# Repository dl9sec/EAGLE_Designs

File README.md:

# EAGLE Designs
Some designs created with EAGLE 6.6.0.

# Contents

<dl>
  <dt>ESP32VGAv2 (License CC BY-SA 4.0)</dt>
  <dd>An ESP-32 DevKitC base board with 6-bit VGA, DAC sound output and PS/2 keyboard connector. The design can be used with FabGL by fdivitto (https://github.com/fdivitto/FabGL) and with ESP32Lib by bitluni (https://github.com/bitluni/ESP32Lib). The folder contains a ready-to-use ZIP-archive with Gerber/Excellon data which can be directly used at JLCPCB.com.</dd>
  <dt>ESP32-XTonUINO/ESP32-XTonUINO_Buttons (License GPL-3.0-only)</dt>
  <dd>An ESP-32 DevKitC base board which can be used for a TonUINO player (e.g. with adapted sources of CKUL's TonUINO-ESP project at https://github.com/CKUL/TonUINO-ESP32 or one of its forks). The base design is extended by capacitive touch buttons and a relay which can be used e.g. for a door opener. The design uses a module for charging a LiPo/LiIon recharchable battery and a boost converter module to supply the board from the battery. The folder contains ready-to-use ZIP-archives with Gerber/Excellon data which can be directly used at JLCPCB.com.</dd>
  <dt>JLCPCB_CAMjob (License MIT)</dt>
  <dd>A CAM job to generate the Gerber/EXCELLON data for JLCPCB.com in one pass (ZIP the generated files before upload!).</dd>

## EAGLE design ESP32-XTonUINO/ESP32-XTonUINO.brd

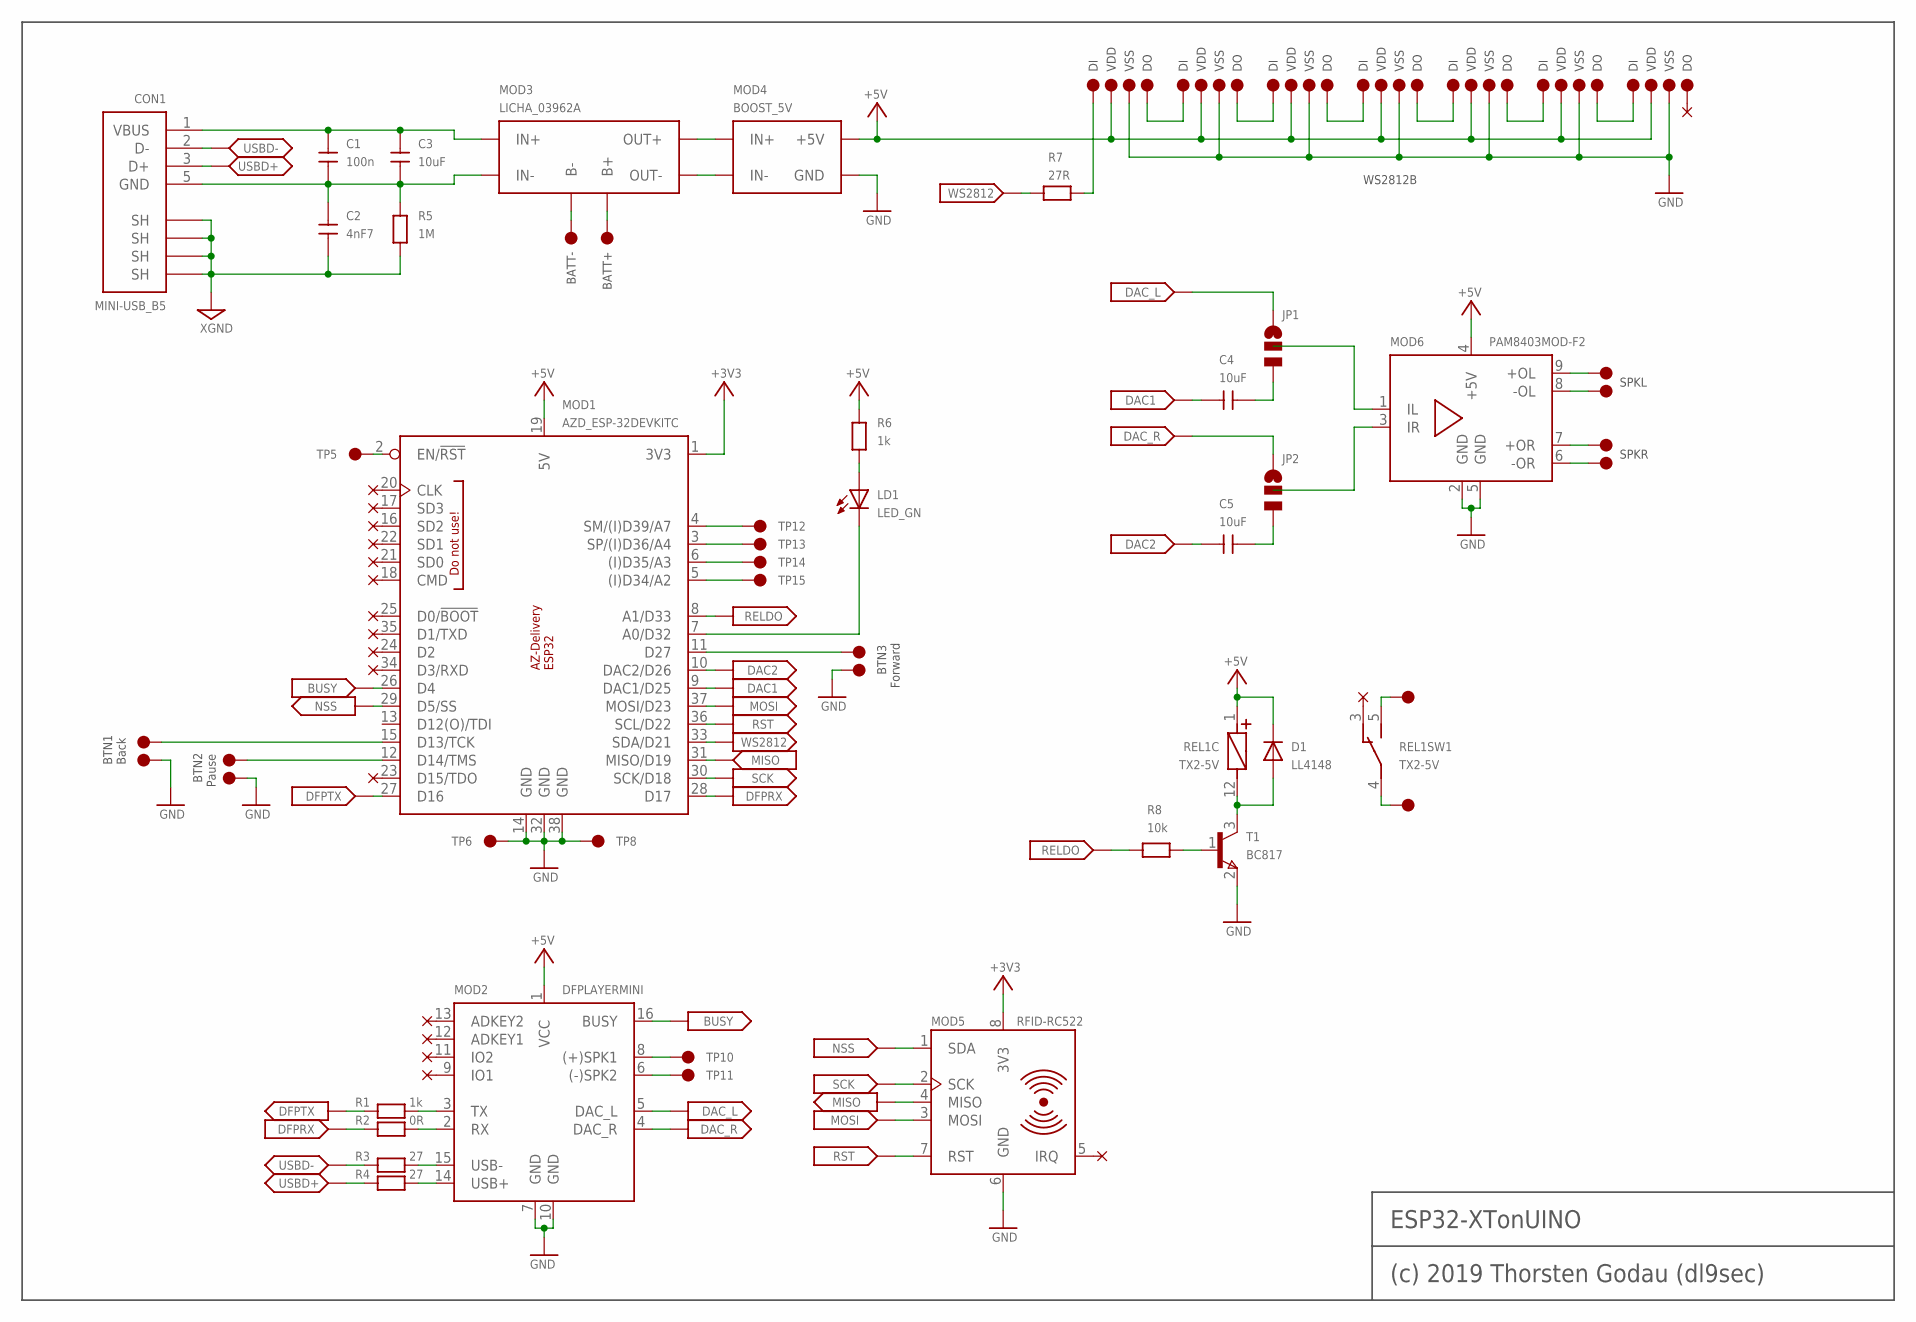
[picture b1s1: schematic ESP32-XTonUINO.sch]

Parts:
C1: 100n; 0805
C2: 4nF7; 0805
C3, C4, C5: 10uF; 0805
CON1: MINI-USB_B5; MINIUSB_B5
D1: LL4148; MINIMELF
JP1, JP2: JUMPER_1X3SMD; JUMPER_1X3_SMD
LD1: LED_GN; LED3MMH
MOD1: AZD_ESP-32DEVKITC
MOD2: DFPLAYERMINI
MOD3: LICHA_03962A
MOD4: BOOST_5V
MOD5: RFID-RC522
MOD6: PAM8403MOD-F2; PAM8403MOD2
R1, R6: 1k; 0805
R2: 0R; 0805
R3, R4: 27; 0805
R5: 1M; 0805
R7: 27R; 0805
R8: 10k; 0805
REL1: TX2-5V; RELTX2
T1: BC817; SOT23
TP1, TP2, TP3, TP4, TP5, TP6, TP7, TP8, TP9, TP12, TP13, TP14, TP15, TP16, TP17, TP18, TP19, TP20, TP21, TP22, TP23, TP24, TP25, TP26, TP27, TP28, TP29, TP30, TP31, TP32, TP33, TP34, TP35, TP36, TP37, TP38, TP39, TP40, TP45, TP48, TP49, TP50, TP51: TESTPINTHT1; TESTPIN_THT1
TP10, TP11, TP41, TP42, TP43, TP44, TP46, TP47: TESTPINTHT2; TESTPIN_THT2

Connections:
+3V3: MOD1.1 (3V3), MOD5.8 (3V3)
+5V: D1.K, MOD1.19 (5V), MOD2.1 (VCC), MOD4.+5V, MOD6.4 (+5V), R6.2, REL1.1 (+), TP19.1, TP23.1, TP27.1, TP31.1, TP35.1, TP39.1, TP49.1
BATT+: MOD3.B+, TP9.1
BATT-: MOD3.B-, TP7.1
BTN1: MOD1.15 (D13/TCK), TP1.1
BTN2: MOD1.12 (D14/TMS), TP3.1
BTN3: MOD1.11 (D27), TP16.1
BUSY: MOD1.26 (D4), MOD2.16 (BUSY)
DAC1: C4.1, MOD1.9 (DAC1/D25)
DAC2: C5.1, MOD1.10 (DAC2/D26)
DAC_L: JP1.1, MOD2.5 (DAC_L)
DAC_R: JP2.1, MOD2.4 (DAC_R)
DFPRX: MOD1.28 (D17), R2.1
DFPTX: MOD1.27 (D16), R1.1
GND: MOD1.14 (GND), MOD1.32 (GND), MOD1.38 (GND), MOD2.7 (GND), MOD2.10 (GND), MOD4.GND, MOD5.6 (GND), MOD6.2 (GND), MOD6.5 (GND), T1.2 (E), TP2.1, TP4.1, TP6.1, TP8.1, TP17.1, TP20.1, TP24.1, TP28.1, TP32.1, TP36.1, TP40.1, TP50.1
MISO: MOD1.31 (MISO/D19), MOD5.4 (MISO)
MOSI: MOD1.37 (MOSI/D23), MOD5.3 (MOSI)
unnamed: C1.1, C2.2, C3.1, CON1.5 (GND), MOD3.IN-, R5.2
unnamed: MOD2.14 (USB+), R4.2
unnamed: MOD1.4 (SM/(I)D39/A7), TP12.1
unnamed: MOD1.3 (SP/(I)D36/A4), TP13.1
unnamed: MOD3.OUT-, MOD4.IN-
unnamed: MOD1.6 ((I)D35/A3), TP14.1
unnamed: MOD1.5 ((I)D34/A2), TP15.1
unnamed: MOD1.2 (EN/!RST!), TP5.1
unnamed: C4.2, JP1.3
unnamed: LD1.A, R6.1
unnamed: JP2.2, MOD6.3 (IR)
unnamed: MOD2.15 (USB-), R3.2
unnamed: JP1.2, MOD6.1 (IL)
unnamed: C5.2, JP2.3
unnamed: TP21.1, TP22.1
unnamed: MOD6.9 (+OL), TP41.1
unnamed: MOD2.2 (RX), R2.2
unnamed: MOD2.3 (TX), R1.2
unnamed: MOD6.8 (-OL), TP42.1
unnamed: MOD6.7 (+OR), TP43.1
unnamed: MOD6.6 (-OR), TP44.1
unnamed: TP25.1, TP26.1
unnamed: TP29.1, TP30.1
unnamed: TP33.1, TP34.1
unnamed: TP37.1, TP38.1
unnamed: TP45.1, TP48.1
unnamed: REL1.4 (COM), TP47.1
unnamed: REL1.5 (NO), TP46.1
unnamed: R7.2, TP18.1
unnamed: D1.A, REL1.12 (-), T1.3 (C)
unnamed: R8.2, T1.1 (B)
NLED: LD1.K, MOD1.7 (A0/D32)
NSS: MOD1.29 (D5/SS), MOD5.1 (SDA)
OUT+: MOD3.OUT+, MOD4.IN+
RELDO: MOD1.8 (A1/D33), R8.1
RST: MOD1.36 (SCL/D22), MOD5.7 (RST)
SCK: MOD1.30 (SCK/D18), MOD5.2 (SCK)
SPK+: MOD2.8 ((+)SPK1), TP10.1
SPK-: MOD2.6 ((-)SPK2), TP11.1
USBD+: CON1.3 (D+), R4.1
USBD-: CON1.2 (D-), R3.1
VBUS: C1.2, C3.2, CON1.1 (VBUS), MOD3.IN+
WS2812: MOD1.33 (SDA/D21), R7.1
XGND: C2.1, CON1.S1 (SH), CON1.S2 (SH), CON1.S3 (SH), CON1.S4 (SH), R5.1

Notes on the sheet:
(c) 2019 Thorsten Godau (dl9sec)
BTN3
BTN2
BTN1
Back
Pause
Forward
VDD
VSS
WS2812B
SPKL
SPKR
BATT-
BATT+
ESP32-XTonUINO

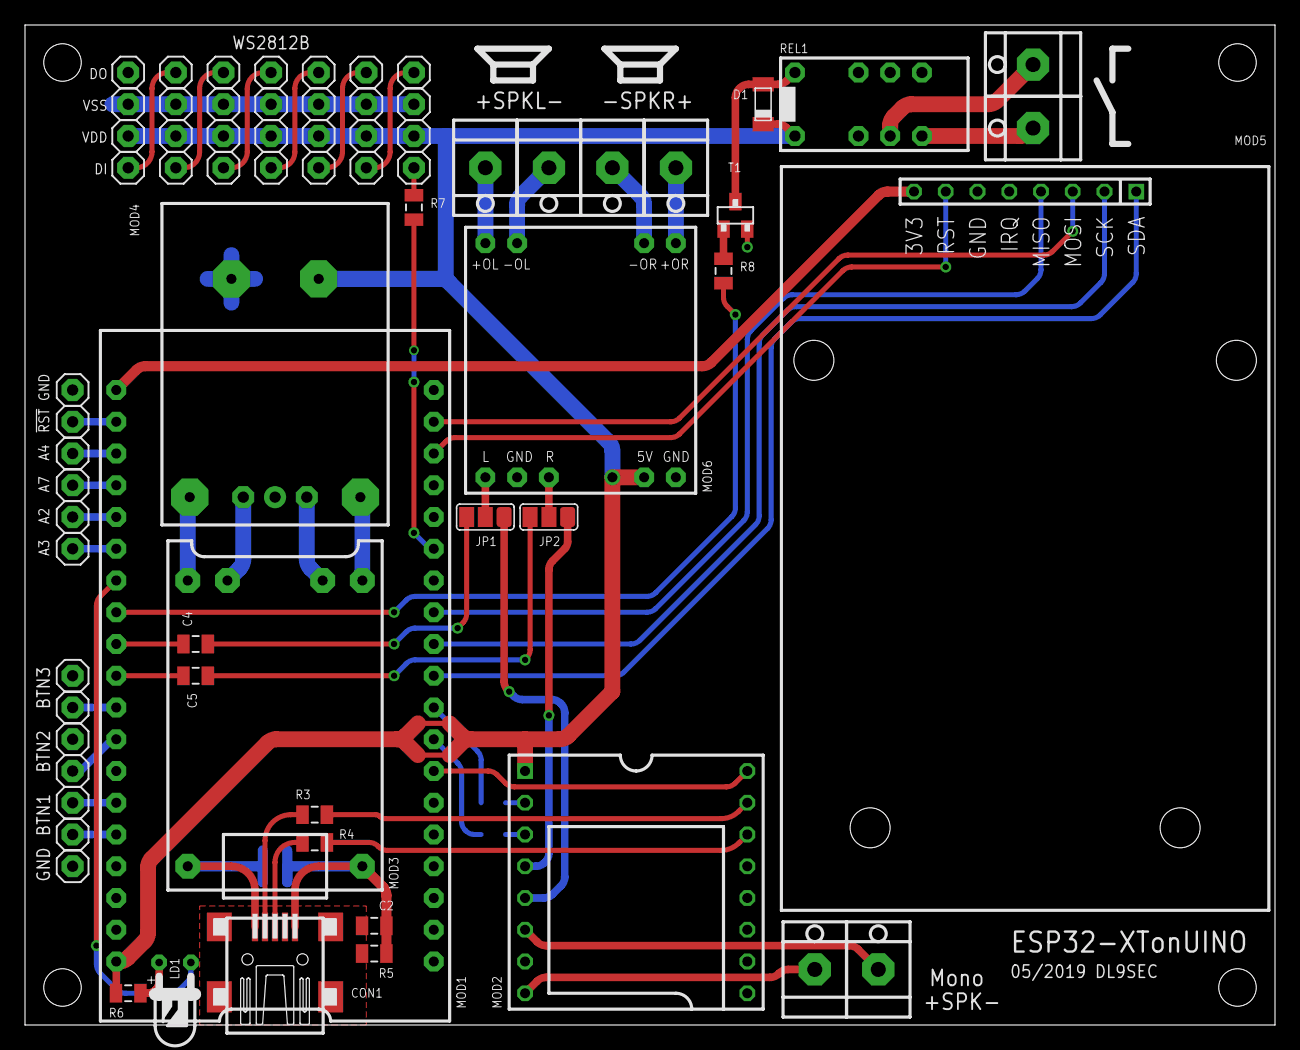
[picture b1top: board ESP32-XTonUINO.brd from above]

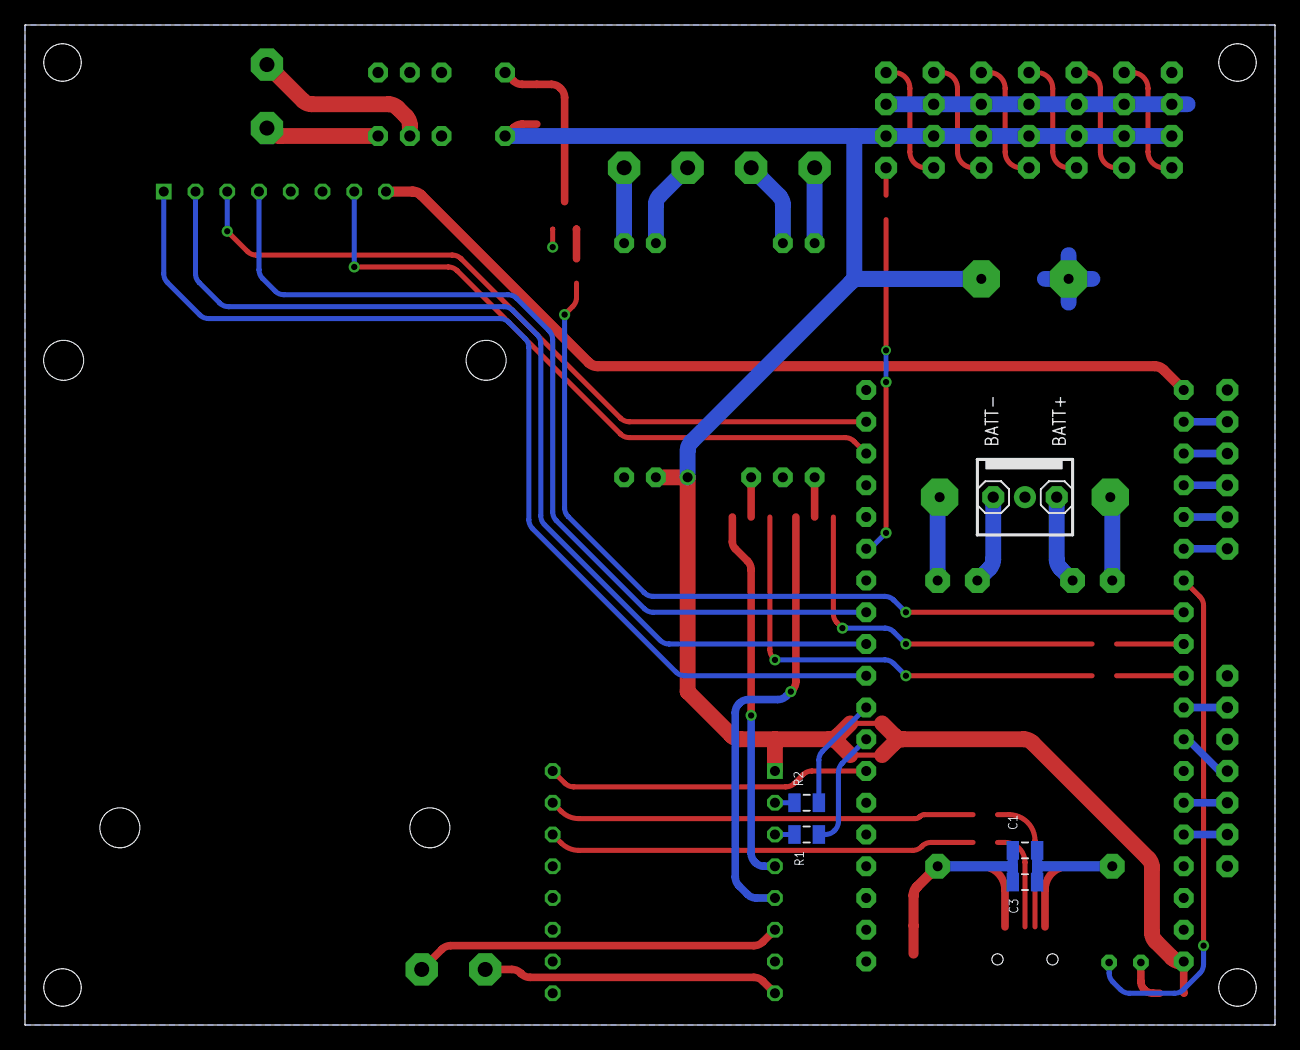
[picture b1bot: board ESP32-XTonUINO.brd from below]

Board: 2 copper layers, 100.0 x 80.0 mm, 77 parts (6 on the bottom side), 61 nets.

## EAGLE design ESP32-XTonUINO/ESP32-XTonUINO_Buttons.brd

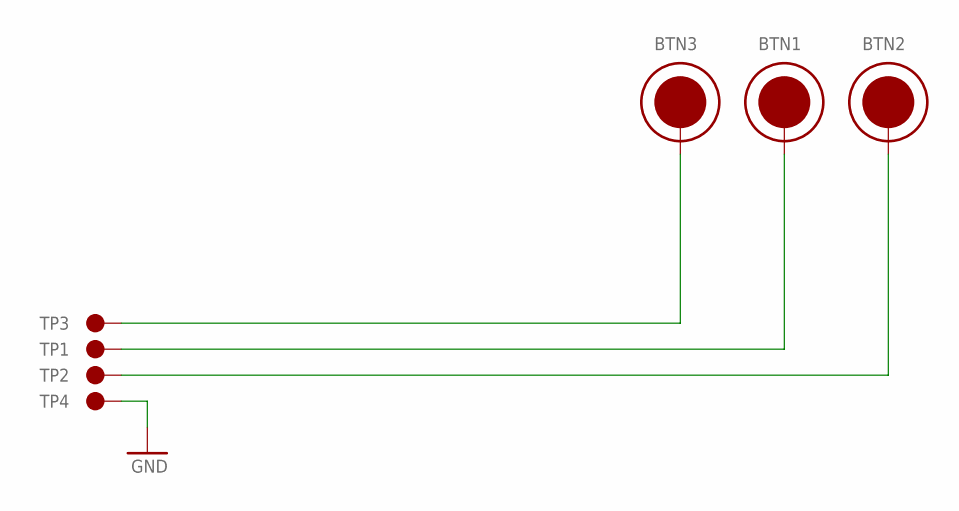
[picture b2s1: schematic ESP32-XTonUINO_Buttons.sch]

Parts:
BTN1, BTN2, BTN3: TOUCHBTN
TP1, TP2, TP3, TP4: TESTPINL; TESTPAD_L

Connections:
GND: TP4.TP
unnamed: BTN3.BTN, TP3.TP
unnamed: BTN1.BTN, TP1.TP
unnamed: BTN2.BTN, TP2.TP

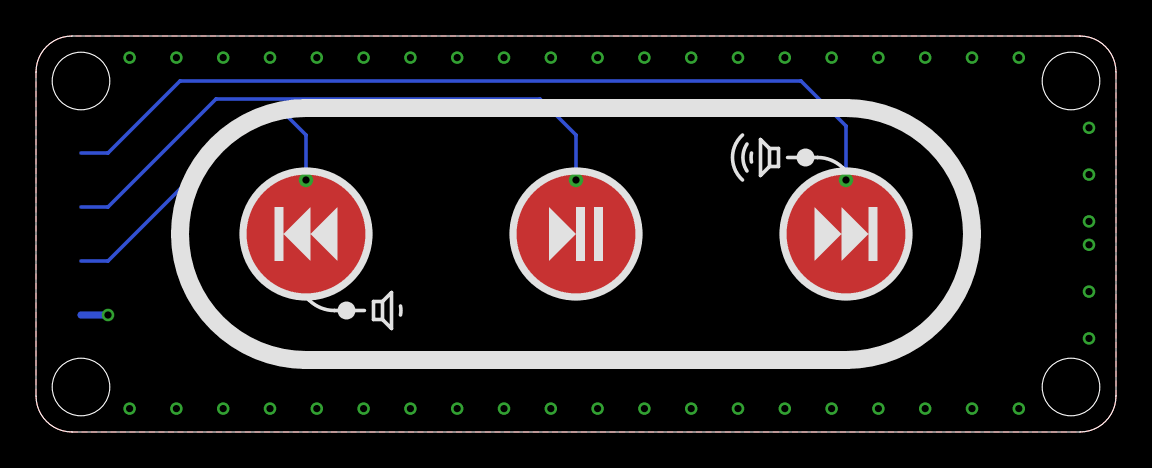
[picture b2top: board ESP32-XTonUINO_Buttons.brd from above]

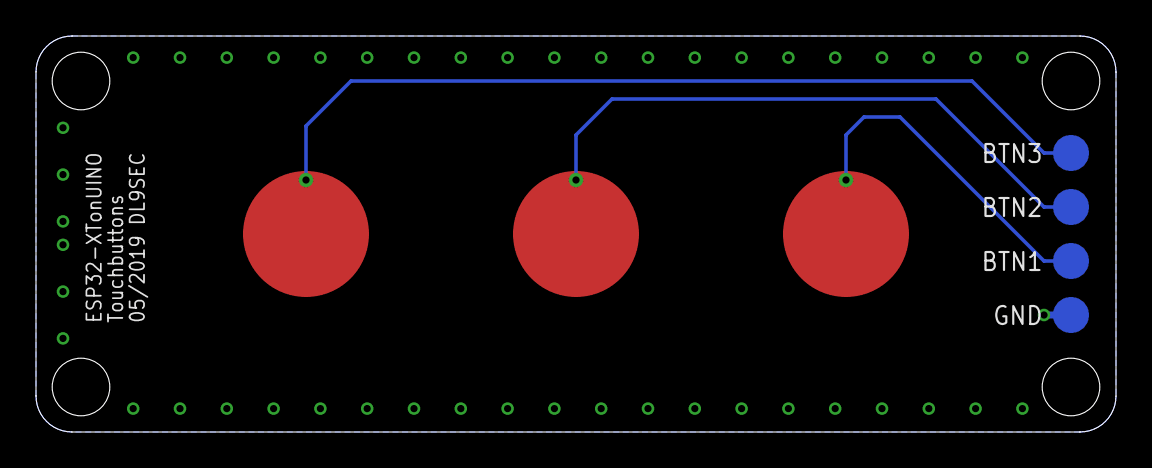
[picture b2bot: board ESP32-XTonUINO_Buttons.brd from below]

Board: 2 copper layers, 60.0 x 22.0 mm, 7 parts (4 on the bottom side), 3 nets.

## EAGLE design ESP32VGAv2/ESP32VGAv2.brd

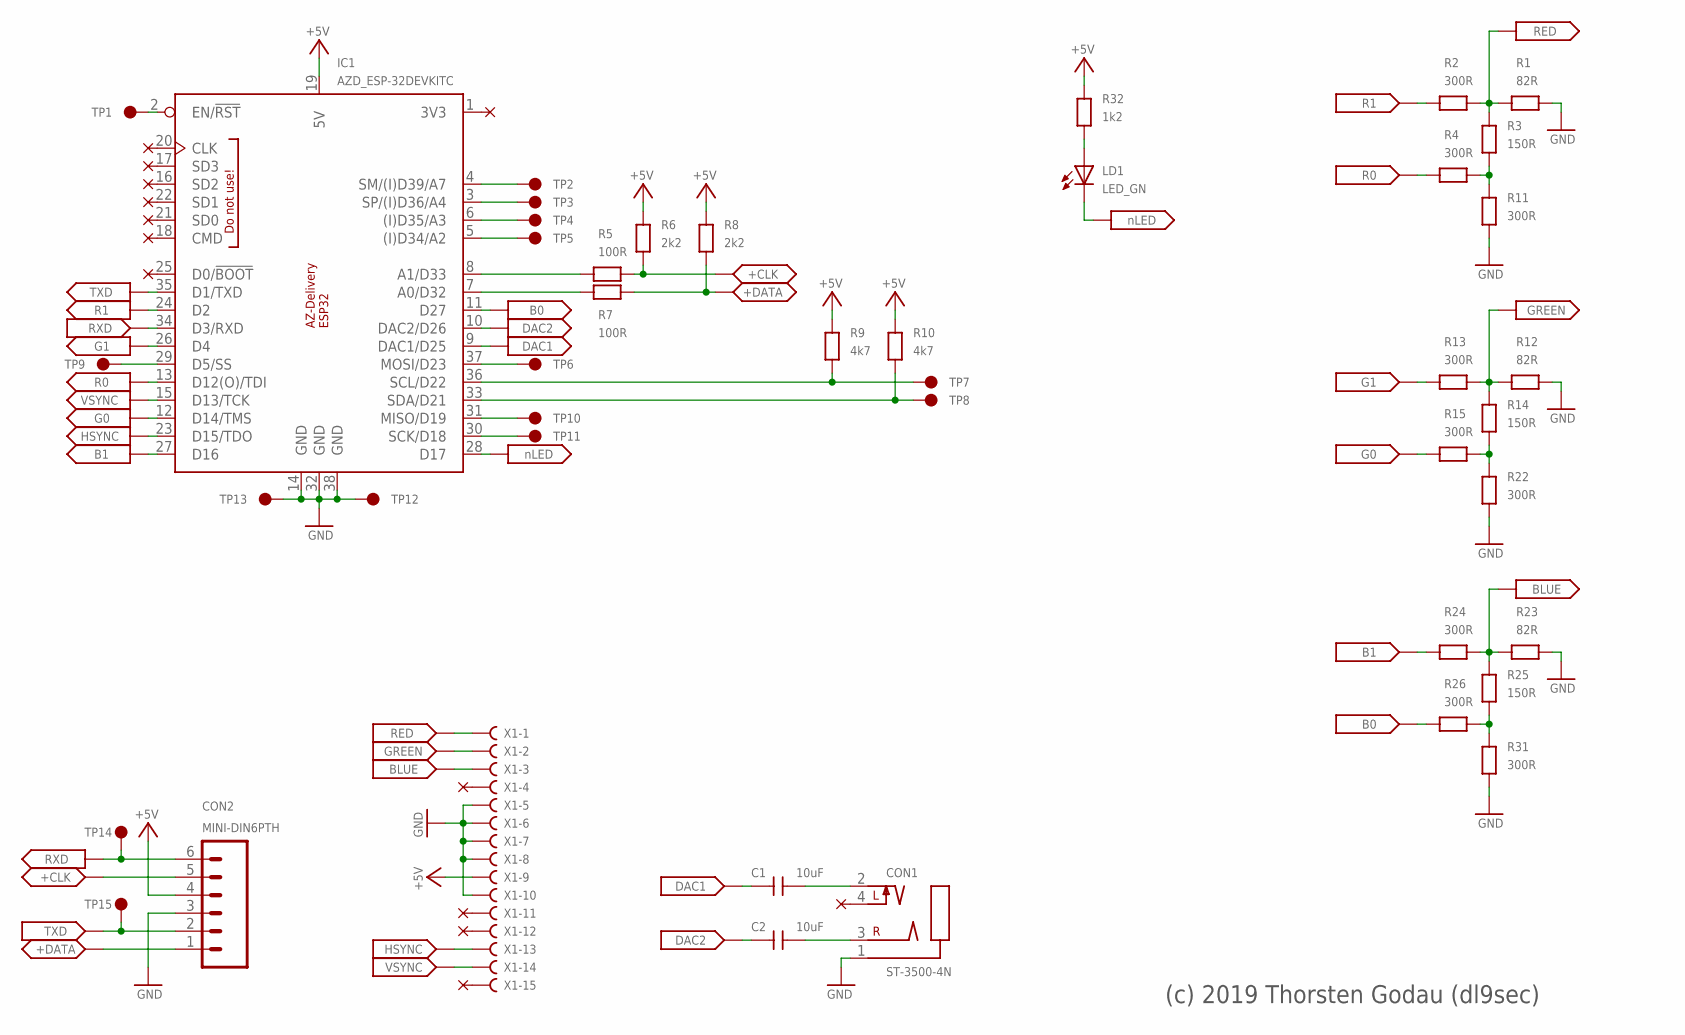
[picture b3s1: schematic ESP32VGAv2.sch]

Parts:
C1, C2: 10uF; 0805
CON1: ST-3500-4N
CON2: MINI-DIN6PTH; MINI-DIN6
IC1: AZD_ESP-32DEVKITC
LD1: LED_GN; LED3MMH
R1, R12, R23: 82R; 0805
R2, R4, R11, R13, R15, R22, R24, R26, R31: 300R; 0805
R3, R14, R25: 150R; 0805
R5, R7: 100R; 0805
R6, R8: 2k2; 0805
R9, R10: 4k7; 0805
R32: 1k2; 0805
TP1, TP2, TP3, TP4, TP5, TP6, TP7, TP8, TP9, TP10, TP11, TP12, TP13, TP14, TP15: TESTPINTHT; TESTPIN_THT
X1: HF15HS; HDF15H

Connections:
+5V: CON2.4, IC1.19 (5V), R6.2, R8.2, R9.2, R10.2, R32.2, X1.9
+CLK: CON2.5, R5.2, R6.1
+DATA: CON2.1, R7.2, R8.1
B0: IC1.11 (D27), R26.1
B1: IC1.27 (D16), R24.1
BLUE: R23.1, R24.2, R25.2, X1.3
DAC1: C1.1, IC1.9 (DAC1/D25)
DAC2: C2.1, IC1.10 (DAC2/D26)
G0: IC1.12 (D14/TMS), R15.1
G1: IC1.26 (D4), R13.1
GND: CON1.1 (COM), CON2.3, IC1.14 (GND), IC1.32 (GND), IC1.38 (GND), R1.2, R11.1, R12.2, R22.1, R23.2, R31.1, TP12.1, TP13.1, X1.5, X1.6, X1.7, X1.8, X1.10
GREEN: R12.1, R13.2, R14.2, X1.2
HSYNC: IC1.23 (D15/TDO), X1.13
KBD_CLK: IC1.8 (A1/D33), R5.1
KBD_DATA: IC1.7 (A0/D32), R7.1
unnamed: R14.1, R15.2, R22.2
unnamed: IC1.4 (SM/(I)D39/A7), TP2.1
unnamed: IC1.3 (SP/(I)D36/A4), TP3.1
unnamed: R3.1, R4.2, R11.2
unnamed: IC1.6 ((I)D35/A3), TP4.1
unnamed: IC1.5 ((I)D34/A2), TP5.1
unnamed: IC1.2 (EN/!RST!), TP1.1
unnamed: C1.2, CON1.2 (L)
unnamed: LD1.A, R32.1
unnamed: IC1.29 (D5/SS), TP9.1
unnamed: R25.1, R26.2, R31.2
unnamed: IC1.30 (SCK/D18), TP11.1
unnamed: IC1.31 (MISO/D19), TP10.1
unnamed: C2.2, CON1.3 (R)
unnamed: IC1.33 (SDA/D21), R10.1, TP8.1
unnamed: IC1.36 (SCL/D22), R9.1, TP7.1
unnamed: IC1.37 (MOSI/D23), TP6.1
NLED: IC1.28 (D17), LD1.K
R0: IC1.13 (D12(O)/TDI), R4.1
R1: IC1.24 (D2), R2.1
RED: R1.1, R2.2, R3.2, X1.1
RXD: CON2.6, IC1.34 (D3/RXD), TP14.1
TXD: CON2.2, IC1.35 (D1/TXD), TP15.1
VSYNC: IC1.15 (D13/TCK), X1.14

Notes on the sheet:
(c) 2019 Thorsten Godau (dl9sec)

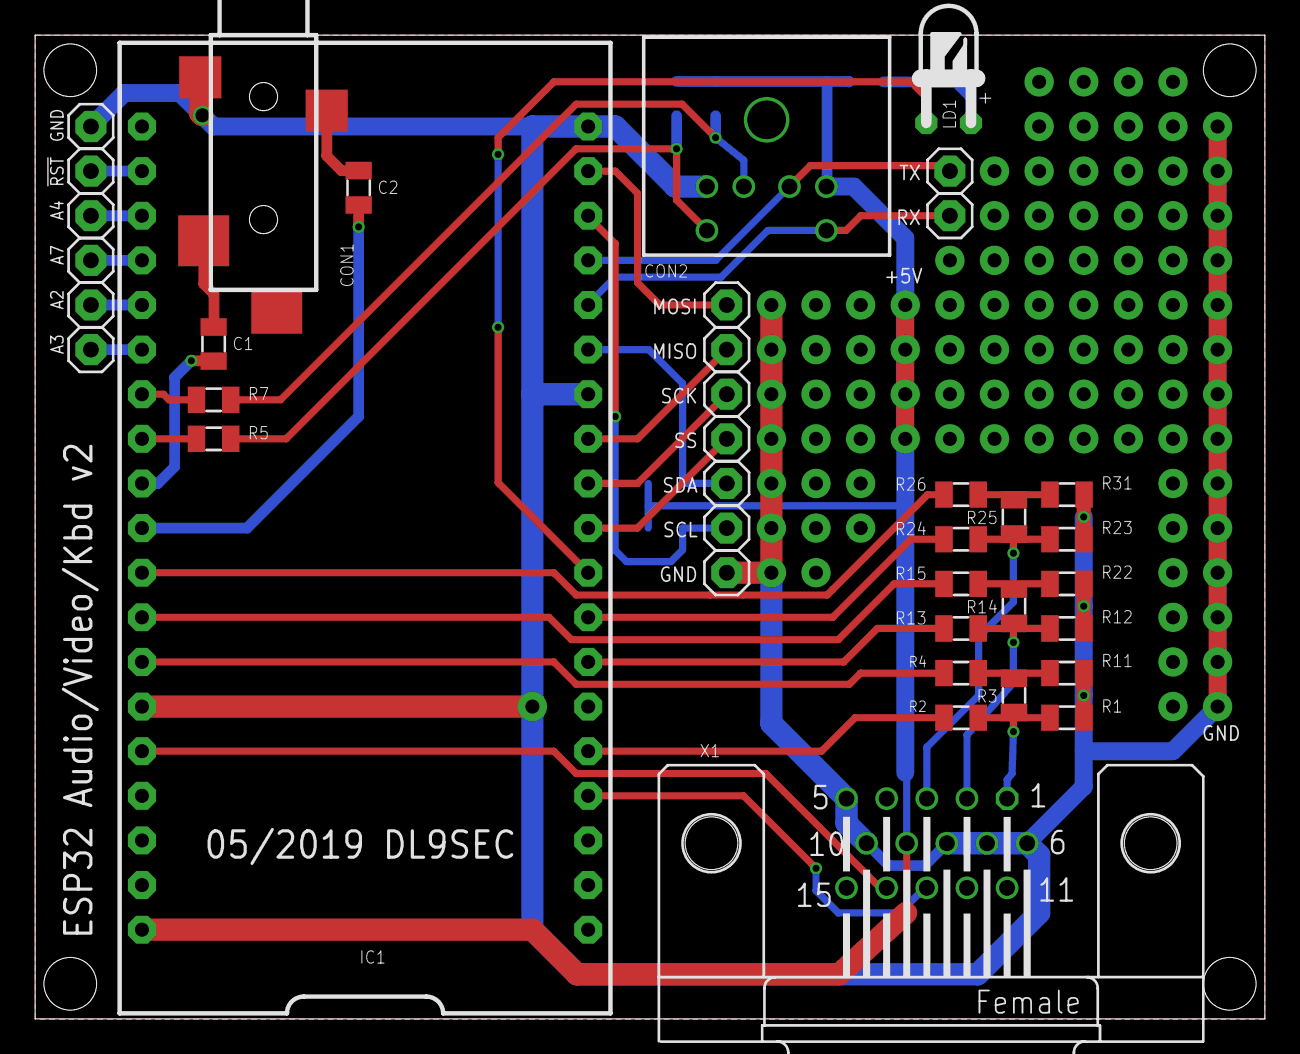
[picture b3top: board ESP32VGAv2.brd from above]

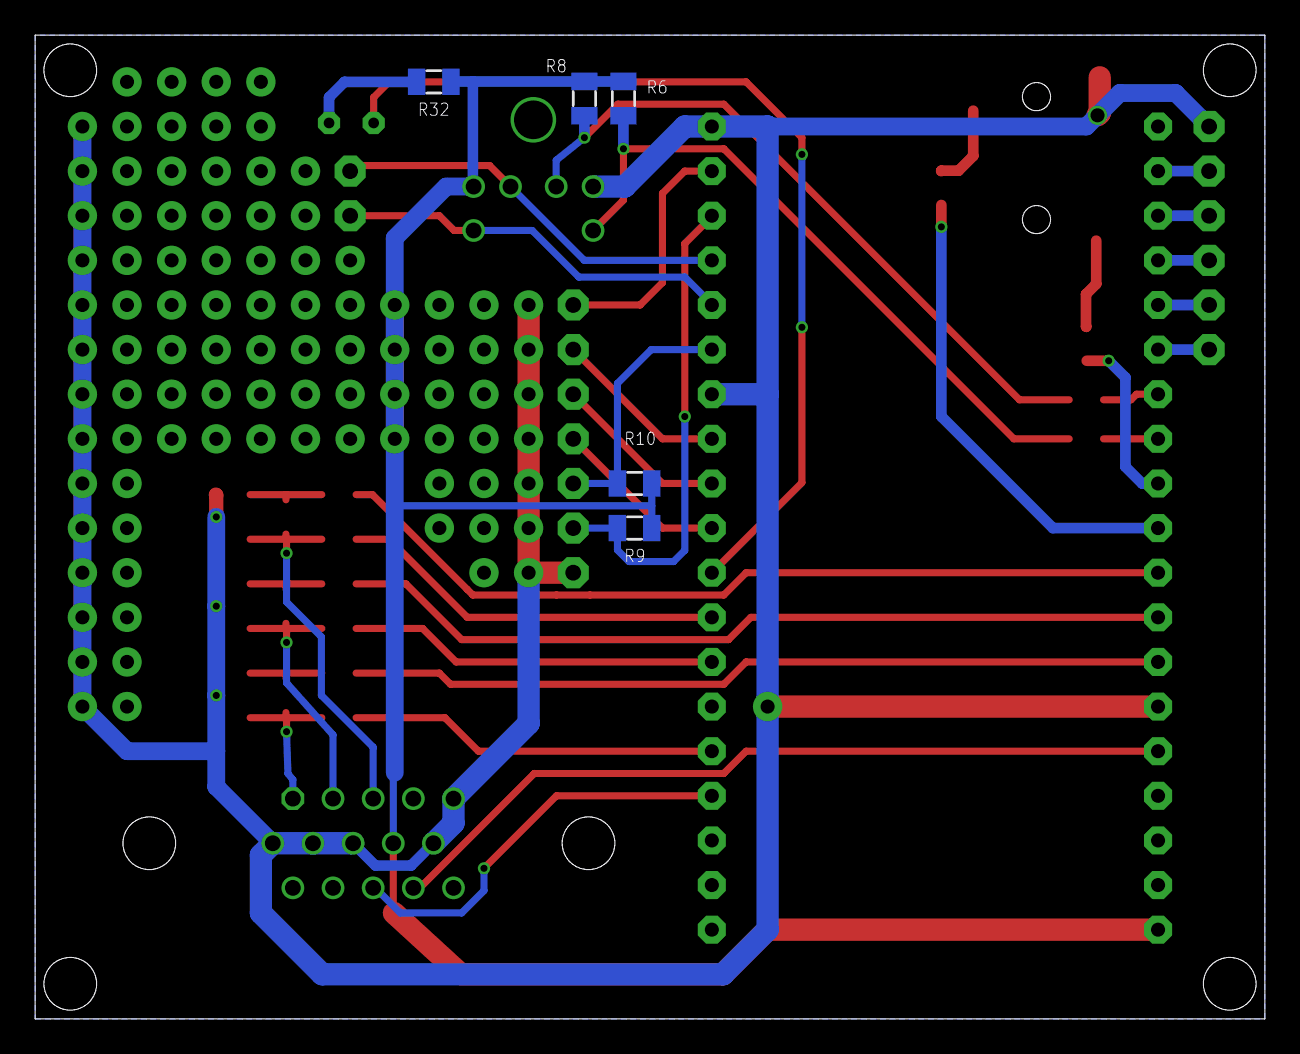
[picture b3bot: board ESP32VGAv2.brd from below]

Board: 2 copper layers, 70.0 x 56.0 mm, 44 parts (5 on the bottom side), 39 nets.

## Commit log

2019-05-25 ESP32VGAv2 uploaded
2019-05-25 Gerber/EXCELLON data added
2019-05-25 Update LICENSE
2019-05-25 CAM job for jlcpvb.com added
2019-05-25 Create test
2019-05-25 Renamed folder
2019-05-30 Added the ESP32-XTonUINO design
2019-06-30 Added derived application 'ESP32DoorUnlock'
    Views, mechanical contruction files and Arduino code for the PCB.
2019-07-09 Update LICENSE
    Changed to CC BY-SA 4.0
2019-07-16 Value enabled
